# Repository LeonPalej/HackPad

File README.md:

<h1>SleekPad</h1>
<p>SleekPad is a simple and sleek stream deck type of micropad containing 9 buttons in total, 8 switches and 1 rotary switch, it also contains a horizontal knob compared to the usual vertical one, the design also contains programmable RGB and a programmable Display. </p>

<h2>Features:</h2>
<ul>
  <li>Sleek case design on a 25 degree angle</li> <li>128x32 OLED Display</li>
  <li>8 SK6812 MINI-E LEDs</li>
  <li>8 Switches</li>
  <li>1 EC11E Rotary encoder (with switch!)</li>
</ul>

<h2>CAD Model:</h2>
<p>The design is made up of 3 layers, the top, middle and bottom, they all join together with the PCB with 4 M3 Bolts screwing into heatset inserts, the board is on a 25 degree angle to mimic the stream deck designs. </p>

<h5><i>Made in Fusion360.</i></h5>

<h2>PCB Model:</h2>
<p>This is the pcb I designed, I have nothing much to say about it other than that its my first pcb and im proud of it.</p>
<p>Schematic:</p>

<br>
<p>PCB:</p> 
<h5><i>Made in KiCad.</i></h5>
<h2>Firmware:</h2>

<p>I made the firmware with kmk, idk if it works because I need to get the materials to build this first and test it out , I plan to make the display, display time and have some functions that change its display depending on the buttons you press or probably go to QMK so i can make a custom app to control it.</p>

<h2>BOM:</h2>
<table>
  <thead>
    <tr>
      <th>Amount</th>
      <th>Component / Description</th>
    </tr>
  </thead>
  <tbody>
    <tr>
      <td>8x</td>
      <td>MX-Style switches</td>
    </tr>
    <tr>
      <td>8x</td>
      <td>White blank DSA keycaps</td>
    </tr>
    <tr>
      <td>9x</td>
      <td>1N4148 Diodes</td>
    </tr>
    <tr>
      <td>8x</td>
      <td>SK6812 MINI-E LEDs</td>
    </tr>
    <tr>
      <td>1x</td>
      <td>EC11 Rotary Encoder</td>
    </tr>
    <tr>
      <td>1x</td>
      <td>Unsoldered Seeed XIAO RP2040</td>
    </tr>
    <tr>
      <td>1x</td>
      <td>0.91 inch OLED display</td>
    </tr>
    <tr>
      <td>1x</td>
      <td>PCB</td>
    </tr>
    <tr>
      <td>5x</td>
      <td>M3x16mm SHCS Bolts</td>
    </tr>
    <tr>
      <td>4x</td>
      <td>M3x5mmx4mm heatset inserts</td>
    </tr>
    <tr>
      <td>1x</td>
      <td>Case Top</td>
    </tr>
    <tr>
      <td>1x</td>
      <td>Case Middle</td>
    </tr>
    <tr>
      <td>1x</td>
      <td>Case Bottom</td>
    </tr>
    <tr>
      <td>1x</td>
      <td>Knob</td>
    </tr>
    <tr>
      <td>1x</td>
      <td>hexagonal M3 DIN934 100/1 nut (I have)</td>
    </tr>
  </tbody>
</table>

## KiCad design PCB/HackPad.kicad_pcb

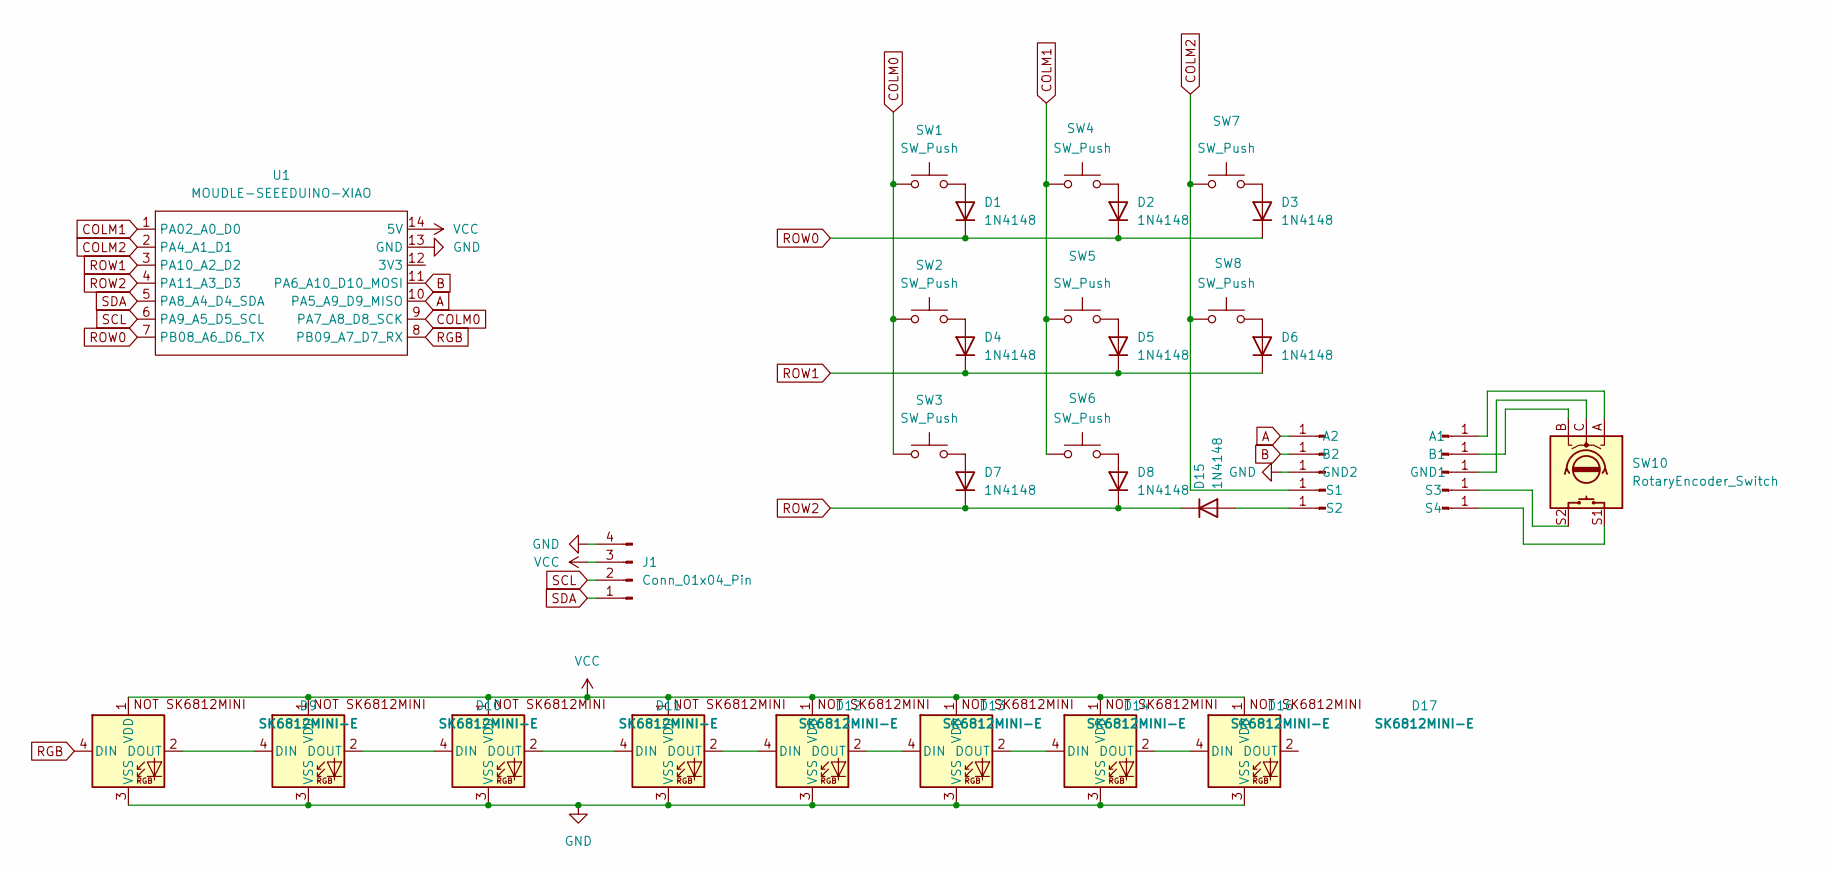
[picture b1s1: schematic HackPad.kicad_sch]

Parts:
A1, A2: Conn_01x01_Pin; SolderWirePad_1x01_SMD_2x4mm
B1, B2: Conn_01x01_Pin; SolderWirePad_1x01_SMD_2x4mm
D1, D2, D3, D4, D5, D6, D7, D8, D15: 1N4148; D_DO-35_SOD27_P7.62mm_Horizontal
D9, D10, D11, D12, D13, D14, D16, D17: SK6812MINI-E; LED_SK6812MINI_PLCC4_3.5x3.5mm_P1.75mm
GND1, GND2: Conn_01x01_Pin; SolderWirePad_1x01_SMD_2x4mm
J1: Conn_01x04_Pin; PinSocket_1x04_P2.54mm_Vertical
S1, S2, S3, S4: Conn_01x01_Pin; SolderWirePad_1x01_SMD_2x4mm
SW1, SW2, SW3, SW4, SW5, SW6, SW7, SW8: SW_Push; SW_Cherry_MX_1.00u_PCB
SW10: RotaryEncoder_Switch; RotaryEncoder_Alps_EC11E-Switch_Vertical_H20mm
U1: MOUDLE-SEEEDUINO-XIAO; XIAO-Generic-Hybrid-14P-2.54-21X17.8MM

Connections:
A: A2.1 (Pin_1_1), U1.10 (PA5_A9_D9_MISO)
B: B2.1 (Pin_1_1), U1.11 (PA6_A10_D10_MOSI)
COLM0: SW1.1, SW2.1, SW3.1, U1.9 (PA7_A8_D8_SCK)
COLM1: SW4.1, SW5.1, SW6.1, U1.1 (PA02_A0_D0)
COLM2: S1.1 (Pin_1_1), SW7.1, SW8.1, U1.2 (PA4_A1_D1)
GND: D9.3 (VSS), D10.3 (VSS), D11.3 (VSS), D12.3 (VSS), D13.3 (VSS), D14.3 (VSS), D16.3 (VSS), D17.3 (VSS), GND2.1 (Pin_1_1), J1.4, U1.13 (GND)
unnamed: A1.1 (Pin_1_1), SW10.A
unnamed: B1.1 (Pin_1_1), SW10.B
unnamed: D1.2 (A), SW1.2
unnamed: D2.2 (A), SW4.2
unnamed: D3.2 (A), SW7.2
unnamed: D4.2 (A), SW2.2
unnamed: D5.2 (A), SW5.2
unnamed: D6.2 (A), SW8.2
unnamed: D7.2 (A), SW3.2
unnamed: D8.2 (A), SW6.2
unnamed: D9.2 (DOUT), D10.4 (DIN)
unnamed: D10.2 (DOUT), D11.4 (DIN)
unnamed: D11.2 (DOUT), D12.4 (DIN)
unnamed: D12.2 (DOUT), D13.4 (DIN)
unnamed: D13.2 (DOUT), D14.4 (DIN)
unnamed: D14.2 (DOUT), D16.4 (DIN)
unnamed: D15.2 (A), S2.1 (Pin_1_1)
unnamed: D16.2 (DOUT), D17.4 (DIN)
unnamed: GND1.1 (Pin_1_1), SW10.C
unnamed: S3.1 (Pin_1_1), SW10.S2
unnamed: S4.1 (Pin_1_1), SW10.S1
RGB: D9.4 (DIN), U1.8 (PB09_A7_D7_RX)
ROW0: D1.1 (K), D2.1 (K), D3.1 (K), U1.7 (PB08_A6_D6_TX)
ROW1: D4.1 (K), D5.1 (K), D6.1 (K), U1.3 (PA10_A2_D2)
ROW2: D7.1 (K), D8.1 (K), D15.1 (K), U1.4 (PA11_A3_D3)
SCL: J1.2, U1.6 (PA9_A5_D5_SCL)
SDA: J1.1, U1.5 (PA8_A4_D4_SDA)
VCC: D9.1 (VDD), D10.1 (VDD), D11.1 (VDD), D12.1 (VDD), D13.1 (VDD), D14.1 (VDD), D16.1 (VDD), D17.1 (VDD), J1.3, U1.14 (5V)

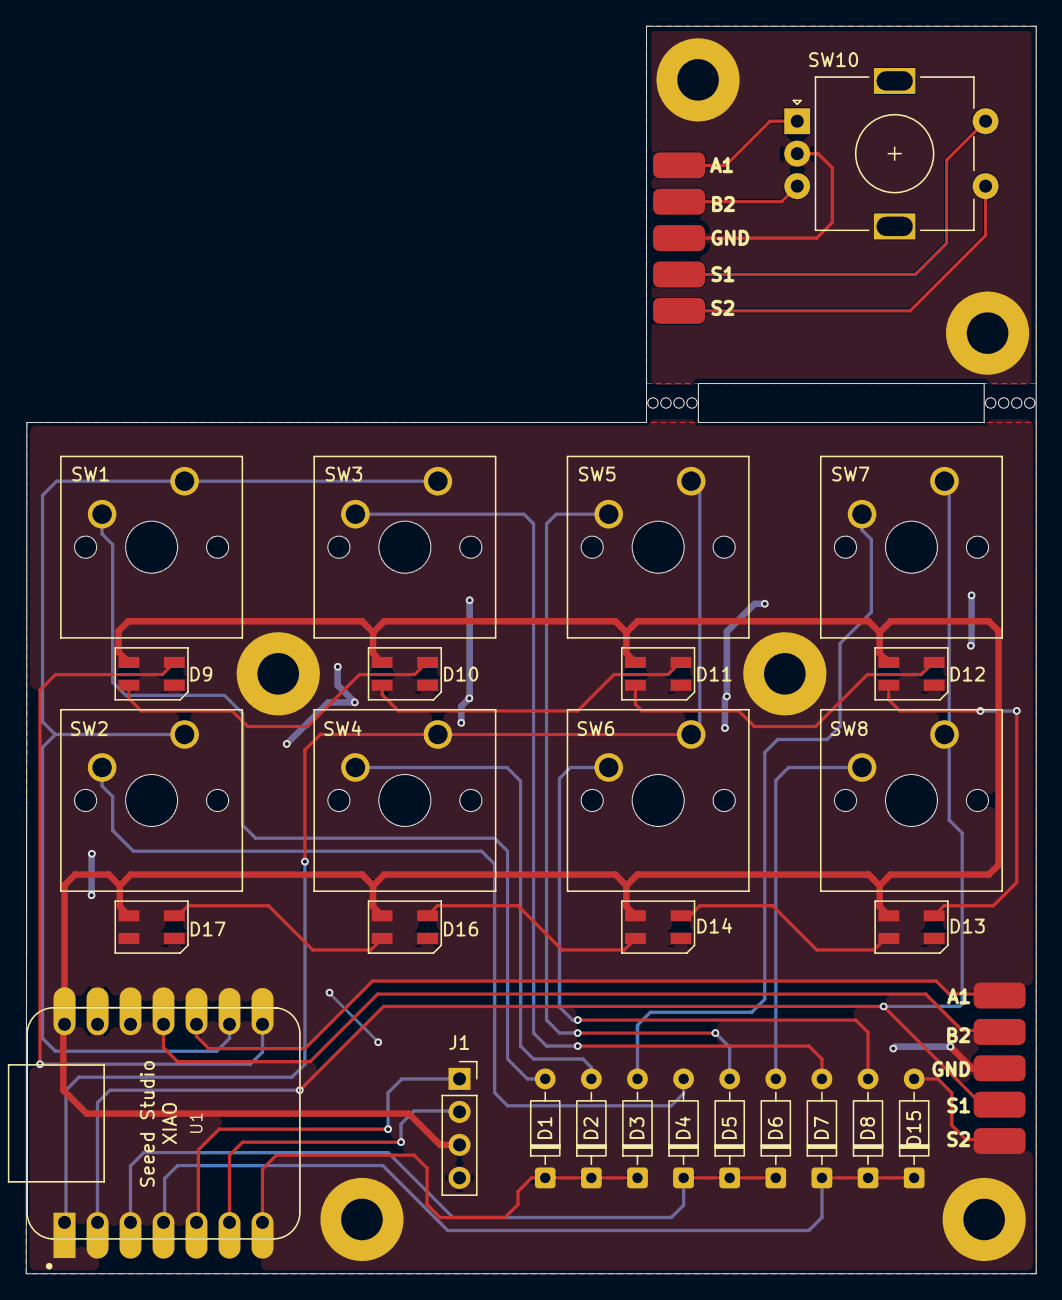
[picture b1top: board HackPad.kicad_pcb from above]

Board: 2 copper layers, 77.7 x 96.0 mm, 38 parts (0 on the bottom side), 34 nets.
